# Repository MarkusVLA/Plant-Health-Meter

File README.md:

## Plant-health-meter
This repository contains Aalto AAN-C2009 project device hardware configuration and embedded software for a plant health monitoring system based on the ESP32c3 SoC.

## Features
- Soil moisture sensing
- Ambient light monitoring
- Temperature and humidity measurement
- Battery-powered operation with charging circuit
- Web interface for monitoring plant health 

## PCB
PCB design done in KiCad.

Schematic: [PDF](PCB/img/schematic.pdf)

## Key Components
- ESP32-C3 microcontroller
- BME280 temperature/humidity sensor
- Custom capacitive soil moisture sensor
- Photodiode and OPA340 based transimpedance amplifier
- ADS1115 16-bit ADC for accurate measurements

## Embedded software
Embedded software is written in C using the ESP-IDF (Espressif IoT Development Framework)
[ESP programming guide](https://docs.espressif.com/projects/esp-idf/en/v5.2.5/esp32c3/get-started/index.html)

## Pin Assignments
See the schematic for detailed I/O connections and sensor bus configuration.

## Setup Instructions
1. Follow the ESP-IDF installation guide
2. Clone this repository
3. In the `main/` folder create `private_config.h` file, with following definitions:
    1. `#define FIREBASE_HOST "xxx.firebasedatabase.app"` - url of the firebase realtime database
    2. `#define FIREBASE_AUTH ""` - authentication token for the firebase - (TODO: not tested yet with protected database)
4. Set ESP32-C3 target in the idf `idf.py set-target esp32c3`
5. Configure the partitions and BLE version `idf.py menuconfig`:
    1. Go to Partition Table → Partition Table and select Custom partition table CSV. Then set the path to `partitions.csv`.
    2. Go to Component Config → Bluetooth → Bluedroid BLE version and choose v4.0.
    3. Save and exit the configuration menu.
6. Build and flash using `idf.py build flash monitor`

## Connection Instructions

1. By default, there are no Wi-Fi credentials set. The device will immediately enter Bluetooth setup mode on boot.

2. For setup, you’ll need a mobile app capable of sending data over BLE, such as **nRF Connect**.

3. When the device is in Bluetooth setup mode, one of its LEDs will begin blinking. You can then find the device in the app under the name:  
   **`PLANT_SENSOR_01`**

4. Press **Connect** to establish a Bluetooth connection.

5. Once connected, look for **Advertised Services** in the device details. Find the characteristic that supports both **Read** and **Write**, and tap the **up arrow (⬆️)** to write data.

6. Select **UTF-8** as the encoding format and send a message with the following structure:  
   ```
   device_id:wifi_ssid:wifi_password
   ```

   For example:  
   ```
   sensor1:mywifi:secret_password
   ```

7. After sending the credentials, the device will restart and attempt to connect to the specified Wi-Fi network.

8. Once connected, sensor data will be sent to Firebase under the provided `device_id`.

---

**Important Notes:**
- `device_id` can contain only **letters, digits, and underscores** (e.g., `plant_sensor_1`).
- If the device fails to connect to Wi-Fi, it will re-enter Bluetooth setup mode on reboot.

## Power Requirements
3.7V Li-ion battery or USB power

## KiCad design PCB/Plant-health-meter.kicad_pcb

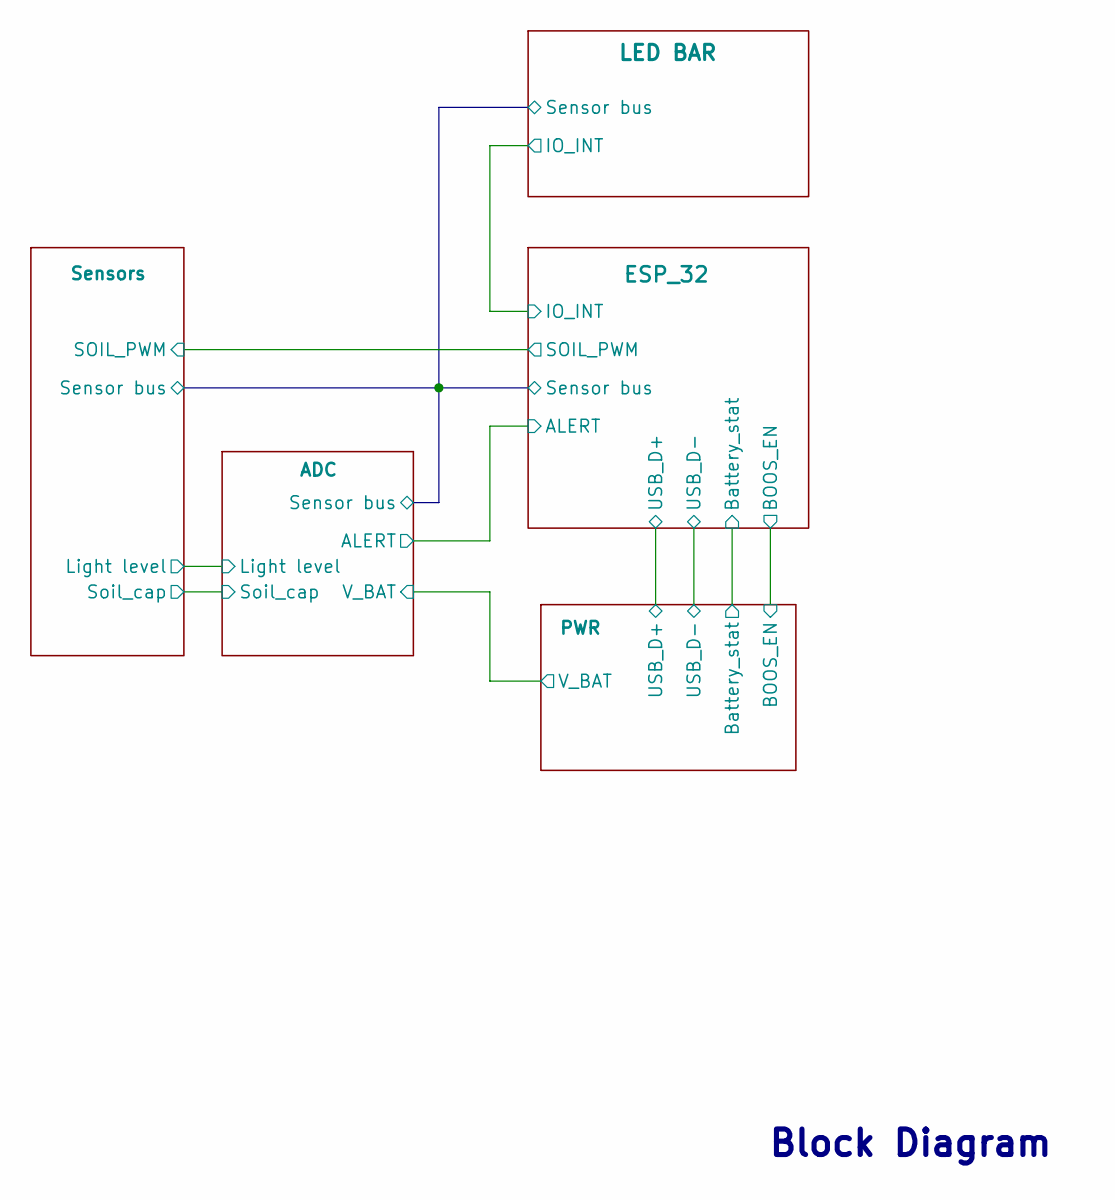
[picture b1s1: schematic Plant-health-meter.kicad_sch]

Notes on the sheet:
Block Diagram

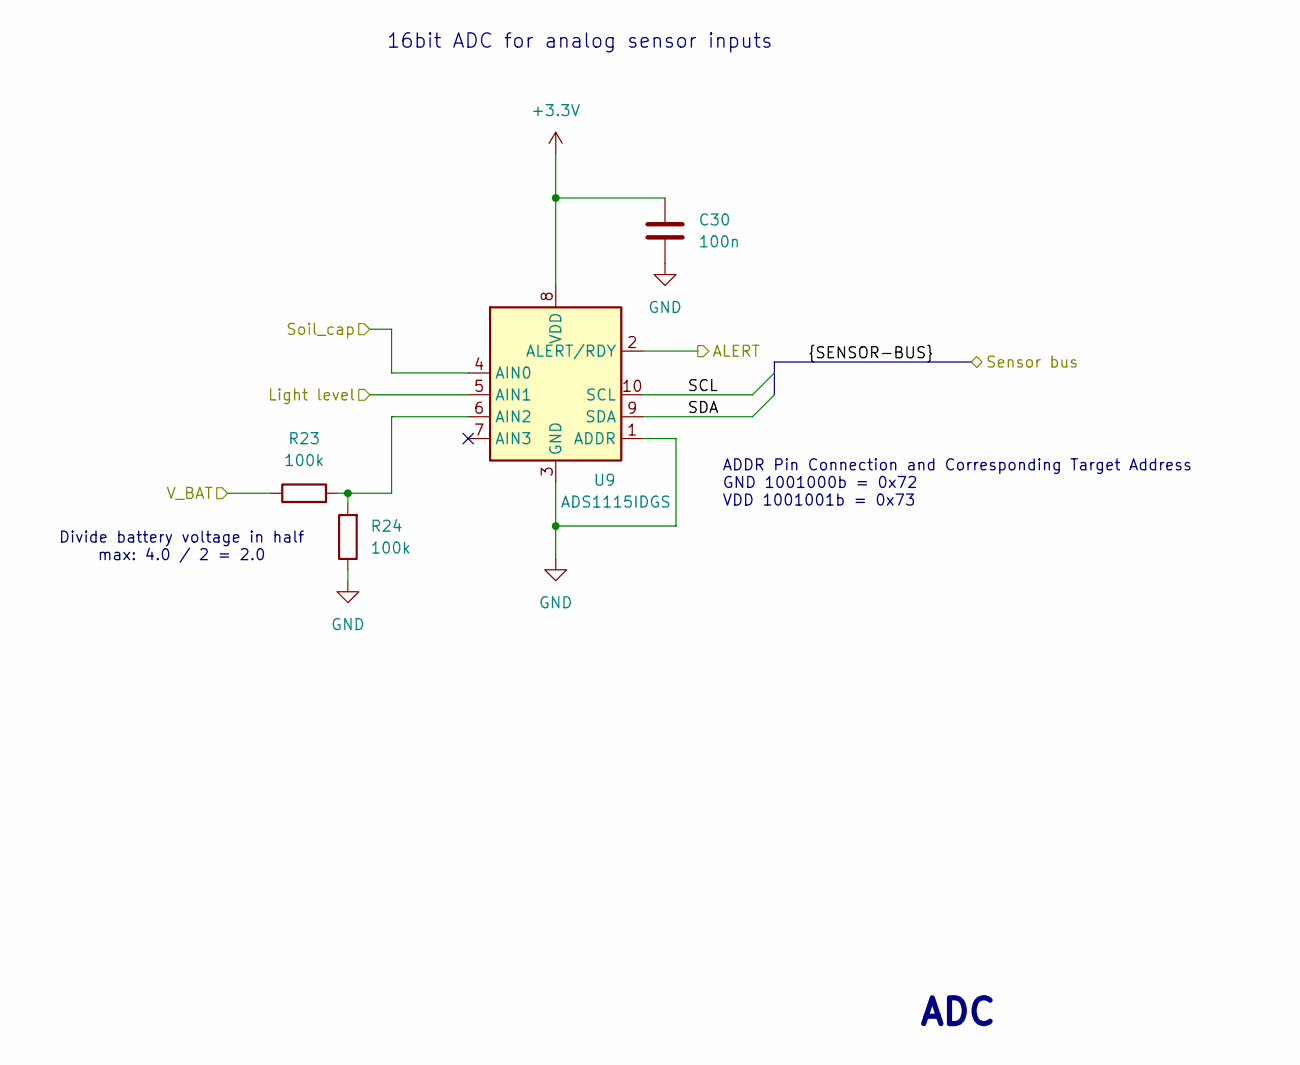
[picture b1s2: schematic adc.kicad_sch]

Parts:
C30: 100n; C_0402_1005Metric
R23, R24: 100k; R_0402_1005Metric
U9: ADS1115IDGS; TSSOP-10_3x3mm_P0.5mm

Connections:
+3.3V: C30.1, U9.8 (VDD); also elsewhere on the board
+BATT: R23.1; also elsewhere on the board
/ADC/ALERT: U9.2 (ALERT/RDY); also elsewhere on the board
/ADC/Light level: U9.5 (AIN1); also elsewhere on the board
/ADC/SCL: U9.10 (SCL); also elsewhere on the board
/ADC/SDA: U9.9 (SDA); also elsewhere on the board
/ADC/Soil_cap: U9.4 (AIN0); also elsewhere on the board
GND: C30.2, R24.1, U9.1 (ADDR), U9.3 (GND); also elsewhere on the board
unnamed: R23.2, R24.2, U9.6 (AIN2)

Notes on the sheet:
ADDR Pin Connection and Corresponding Target Address GND 1001000b = 0x72 VDD 1001001b = 0x73
Divide battery voltage in half max: 4.0 / 2 = 2.0
16bit ADC for analog sensor inputs
ADC

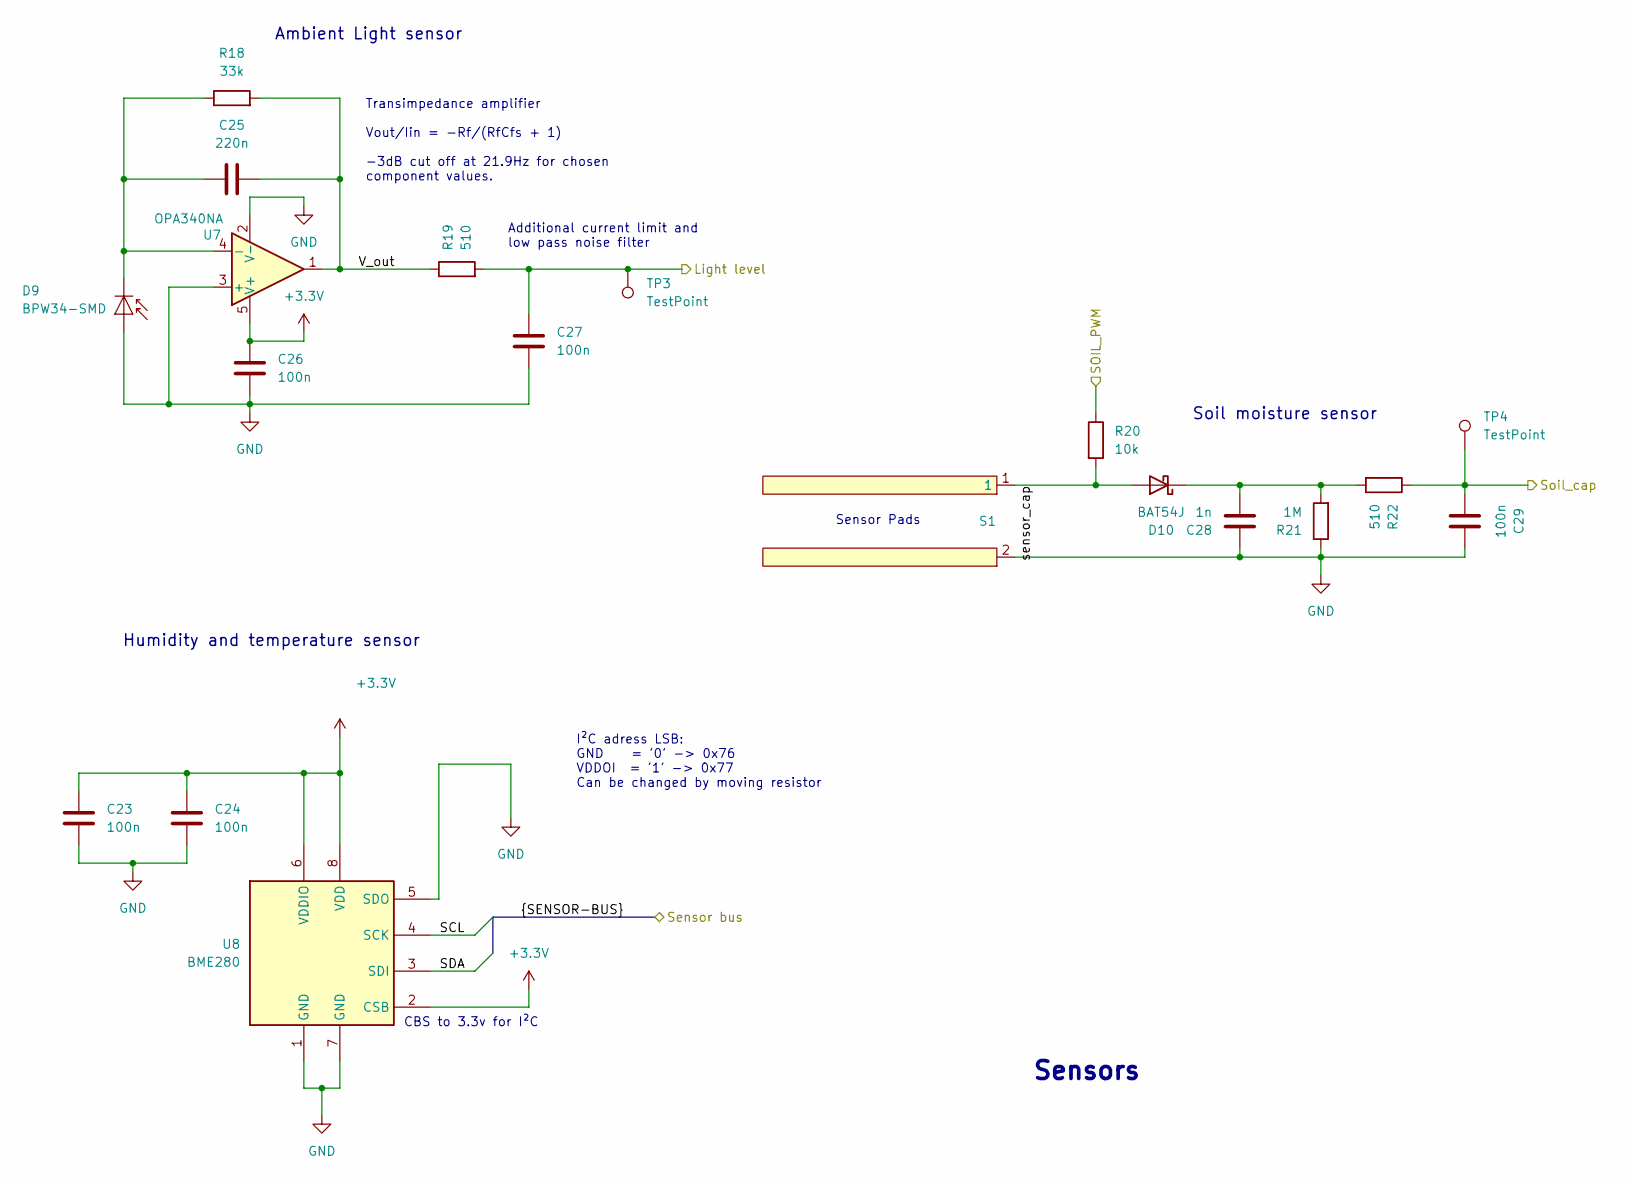
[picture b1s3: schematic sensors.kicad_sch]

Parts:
C23, C24, C26, C27, C29: 100n; C_0402_1005Metric
C25: 220n; C_0402_1005Metric
C28: 1n; C_0402_1005Metric
D9: BPW34-SMD; Osram_BPW34S-SMD
D10: BAT54J; D_SOD-323F
R18: 33k; R_0402_1005Metric
R19, R22: 510; R_0402_1005Metric
R20: 10k; R_0402_1005Metric
R21: 1M; R_0402_1005Metric
S1: Moisture_sensor_pads
TP3, TP4: TestPoint; TestPoint_Pad_D1.0mm
U7: OPA340NA; SOT-23-5
U8: BME280; Bosch_LGA-8_2.5x2.5mm_P0.65mm_ClockwisePinNumbering

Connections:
+3.3V: C23.1, C24.1, C26.1, U7.5 (V+), U8.2 (CSB), U8.6 (VDDIO), U8.8 (VDD); also elsewhere on the board
/ADC/Light level: C27.1, R19.2, TP3.1; also elsewhere on the board
/ADC/SCL: U8.4 (SCK); also elsewhere on the board
/ADC/SDA: U8.3 (SDI); also elsewhere on the board
/ADC/Soil_cap: C29.1, R22.1, TP4.1; also elsewhere on the board
/ESP_32/SOIL_PWM: R20.1; also elsewhere on the board
/Sensors/V_out: C25.2, R18.2, R19.1, U7.1
/Sensors/sensor_cap: D10.2 (A), R20.2, S1.1
GND: C23.2, C24.2, C26.2, C27.2, C28.1, C29.2, D9.2 (A), R21.1, S1.2, U7.2 (V-), U7.3 (+), U8.1 (GND), U8.5 (SDO), U8.7 (GND); also elsewhere on the board
unnamed: C25.1, D9.1 (K), R18.1, U7.4 (-)
unnamed: C28.2, D10.1 (K), R21.2, R22.2

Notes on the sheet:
CBS to 3.3v for I²C
Sensor Pads
I²C adress LSB: GND = '0' -> 0x76 VDDOI = '1' -> 0x77 Can be changed by moving resistor
Soil moisture sensor
Additional current limit and low pass noise filter
Transimpedance amplifier Vout/Iin = -Rf/(RfCfs + 1) -3dB cut off at 21.9Hz for chosen component values.
Humidity and temperature sensor
Sensors
Ambient Light sensor

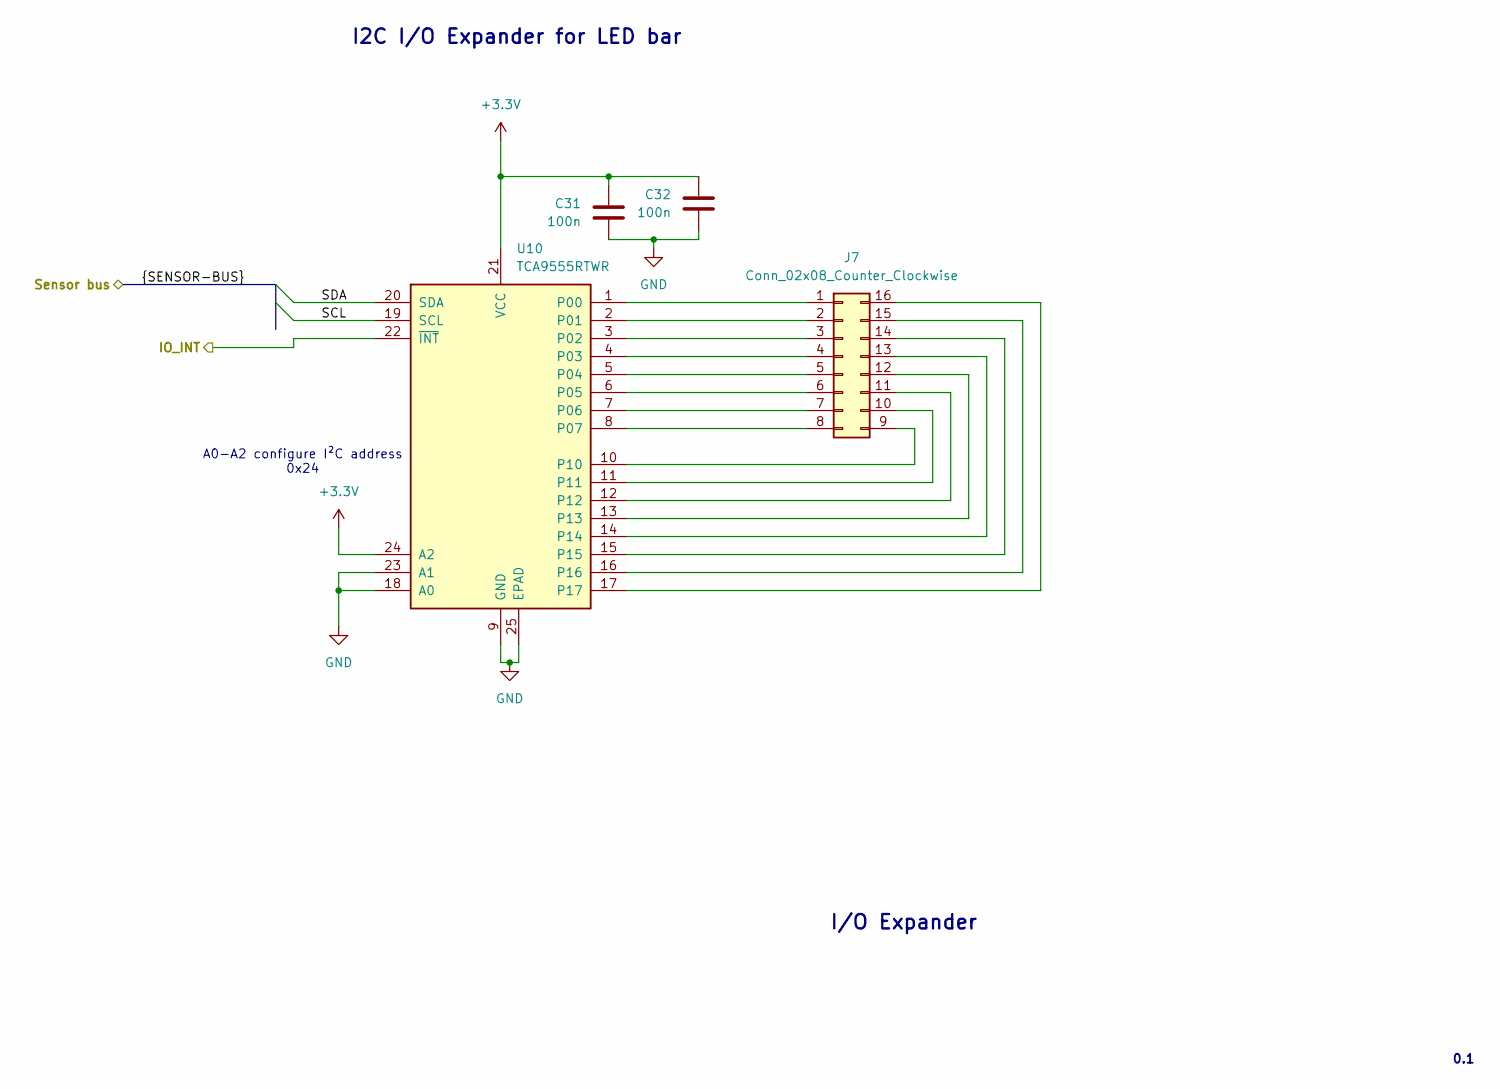
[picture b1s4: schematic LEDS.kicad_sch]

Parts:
C31, C32: 100n; C_0402_1005Metric
J7: Conn_02x08_Counter_Clockwise; PinHeader_2x08_P1.27mm_Vertical_SMD
U10: TCA9555RTWR; WQFN-24-1EP_4x4mm_P0.5mm_EP2.45x2.45mm

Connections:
+3.3V: C31.1, C32.1, U10.21 (VCC), U10.24 (A2); also elsewhere on the board
/ADC/SCL: U10.19 (SCL); also elsewhere on the board
/ADC/SDA: U10.20 (SDA); also elsewhere on the board
/ESP_32/IO_INT: U10.22 (~INT); also elsewhere on the board
GND: C31.2, C32.2, U10.9 (GND), U10.18 (A0), U10.23 (A1), U10.25 (EPAD); also elsewhere on the board
unnamed: J7.1, U10.1 (P00)
unnamed: J7.2, U10.2 (P01)
unnamed: J7.3, U10.3 (P02)
unnamed: J7.4, U10.4 (P03)
unnamed: J7.5, U10.5 (P04)
unnamed: J7.6, U10.6 (P05)
unnamed: J7.7, U10.7 (P06)
unnamed: J7.8, U10.8 (P07)
unnamed: J7.9, U10.10
unnamed: J7.10, U10.11
unnamed: J7.11, U10.12
unnamed: J7.12, U10.13
unnamed: J7.13, U10.14
unnamed: J7.14, U10.15
unnamed: J7.15, U10.16
unnamed: J7.16, U10.17

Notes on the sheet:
0.1
I2C I/O Expander for LED bar
A0-A2 configure I²C address 0x24
I/O Expander

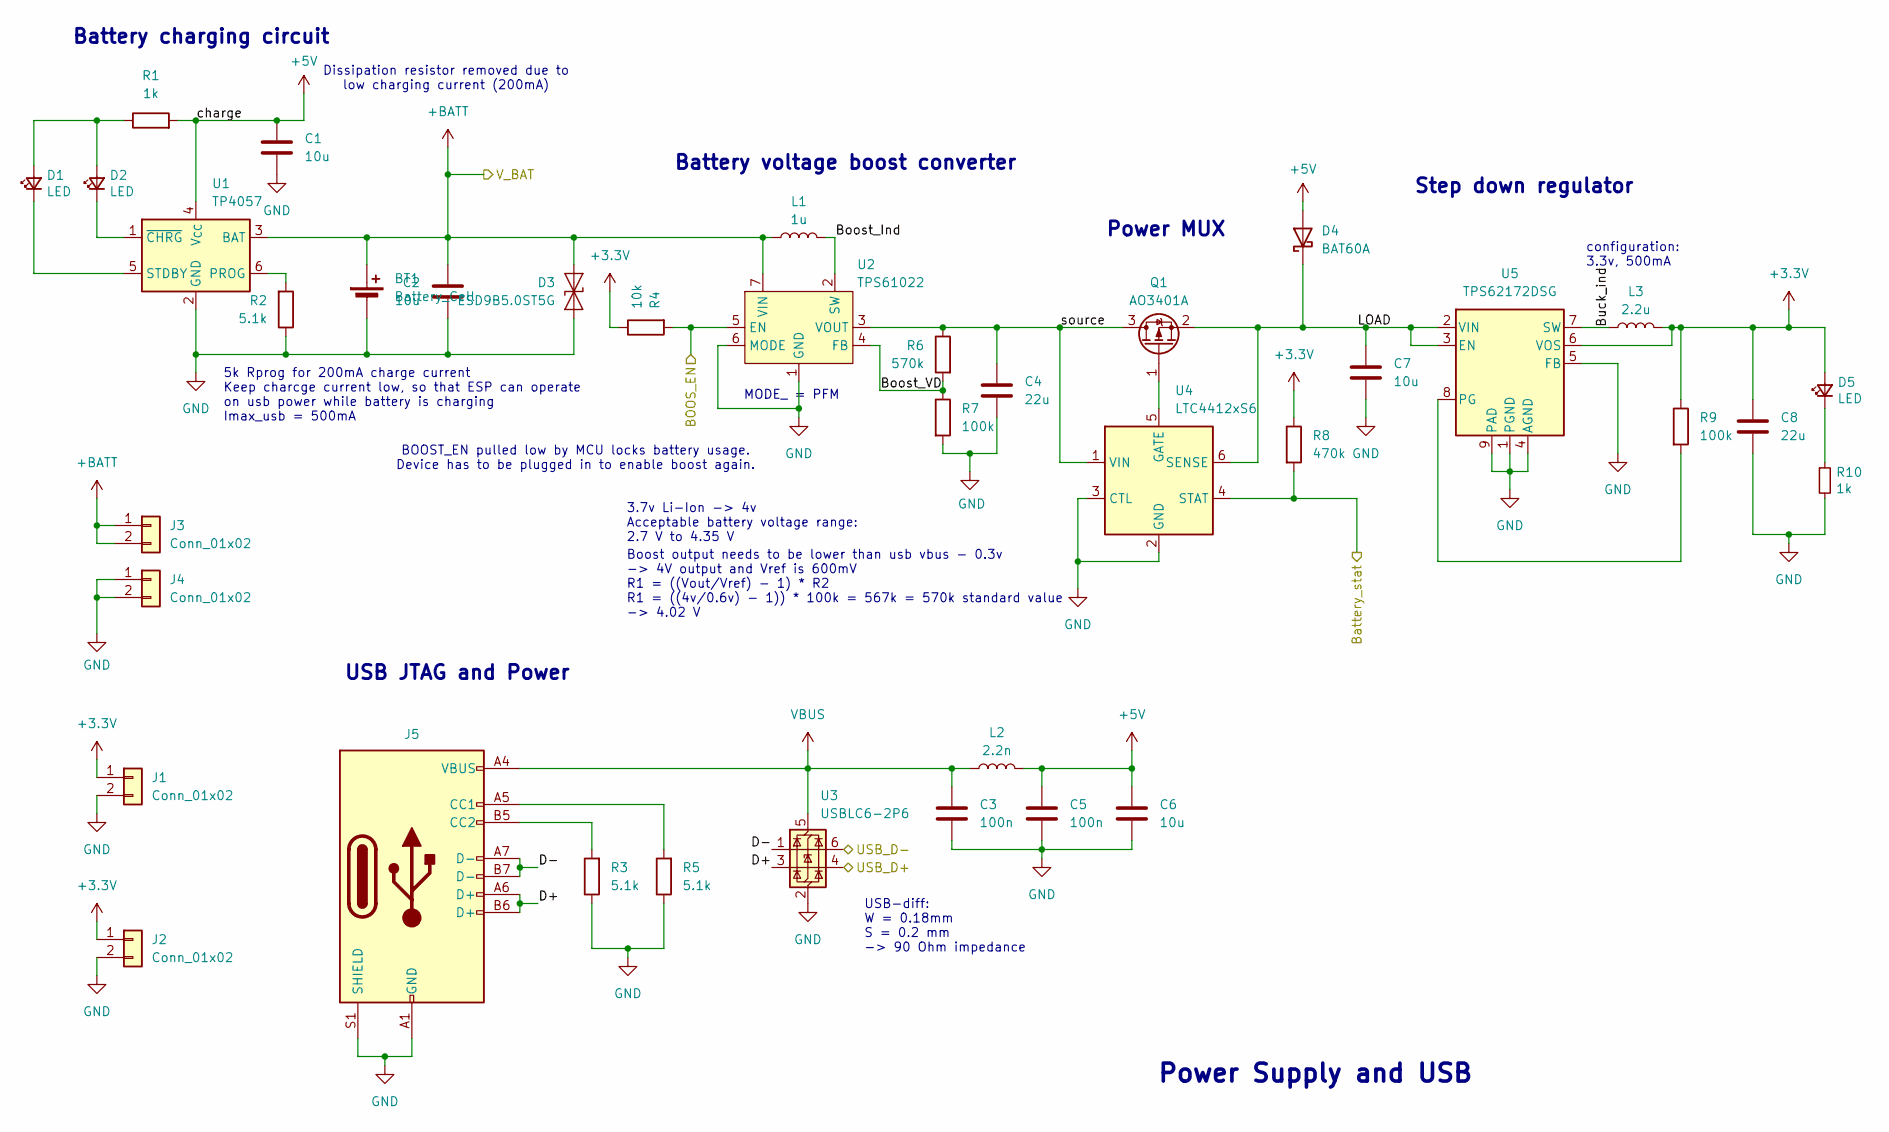
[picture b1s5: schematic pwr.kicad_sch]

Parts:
BT1: Battery_Cell
C1, C2, C6, C7: 10u; C_0603_1608Metric
C3, C5: 100n; C_0402_1005Metric
C4, C8: 22u; C_0805_2012Metric
D1, D2, D5: LED; LED_0805_2012Metric_Pad1.15x1.40mm_HandSolder; LCSC C205445
D3: ESD9B5.0ST5G; D_SOD-923
D4: BAT60A; D_SOD-323
J1, J2, J3, J4: Conn_01x02; PinHeader_1x02_P2.54mm_Vertical
J5: USB_C_Receptacle_USB2.0_14P; USB_C_Receptacle_HRO_TYPE-C-31-M-12
L1: 1u; L_0805_2012Metric
L2: 2.2n; L_0603_1608Metric
L3: 2.2u; L_1008_2520Metric
Q1: AO3401A; SOT-23
R1, R10: 1k; R_0402_1005Metric
R2, R3, R5: 5.1k; R_0402_1005Metric
R4: 10k; R_0402_1005Metric
R6: 570k; R_0402_1005Metric
R7, R9: 100k; R_0402_1005Metric
R8: 470k; R_0402_1005Metric
U1: TP4057; TSOT-23-6
U2: TPS61022; Texas_RWU0007A_VQFN-7_2x2mm_P0.5mm
U3: USBLC6-2P6; SOT-666
U4: LTC4412xS6; TSOT-23-6
U5: TPS62172DSG; WSON-8-1EP_2x2mm_P0.5mm_EP0.9x1.6mm_ThermalVias

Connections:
+3.3V: C8.1, D5.2 (A), J1.1, J2.1, L3.2, R4.1, R8.1, R9.1, U5.6 (VOS); also elsewhere on the board
+5V: C1.1, C5.1, C6.1, D4.2 (A), L2.2, R1.2, U1.4 (V_{CC})
+BATT: BT1.1 (+), C2.1, D3.2 (A2), J3.1, J3.2, L1.1, U1.3 (BAT), U2.7 (VIN); also elsewhere on the board
/ESP_32/BOOS_EN: R4.2, U2.5 (EN); also elsewhere on the board
/ESP_32/Battery_stat: R8.2, U4.4 (STAT); also elsewhere on the board
/ESP_32/USB_D+: U3.4 (I/O2); also elsewhere on the board
/ESP_32/USB_D-: U3.6 (I/O1); also elsewhere on the board
/PWR/Boost_Ind: L1.2, U2.2 (SW)
/PWR/Boost_VD: R6.2, R7.1, U2.4 (FB)
/PWR/Buck_ind: L3.1, U5.7 (SW)
/PWR/D+: J5.A6 (D+), J5.B6 (D+), U3.3 (I/O2)
/PWR/D-: J5.A7 (D-), J5.B7 (D-), U3.1 (I/O1)
/PWR/LOAD: C7.1, D4.1 (K), Q1.2 (S), U4.6 (SENSE), U5.2 (VIN), U5.3 (EN)
/PWR/source: C4.1, Q1.3 (D), R6.1, U2.3 (VOUT), U4.1 (VIN)
GND: BT1.2 (-), C1.2, C2.2, C3.2, C4.2, C5.2, C6.2, C7.2, C8.2, D3.1 (A1), J1.2, J2.2, J4.1, J4.2, J5.A1 (GND), J5.A12 (GND), J5.B1 (GND), J5.B12 (GND), J5.S1 (SHIELD), R2.1, R3.1, R5.1, R7.2, R10.2, U1.2 (GND), U2.1 (GND), U2.6 (MODE), U3.2 (GND), U4.2 (GND), U4.3 (CTL), U5.1 (PGND), U5.4 (AGND), U5.5 (FB), U5.9 (PAD); also elsewhere on the board
unnamed: D1.2 (A), D2.2 (A), R1.1
unnamed: D1.1 (K), U1.5 (STDBY)
unnamed: D2.1 (K), U1.1 (~CHRG)
unnamed: D5.1 (K), R10.1
unnamed: J5.A5 (CC1), R5.2
unnamed: J5.B5 (CC2), R3.2
unnamed: Q1.1 (G), U4.5 (GATE)
unnamed: R2.2, U1.6 (PROG)
unnamed: R9.2, U5.8 (PG)
VBUS: C3.1, J5.A4 (VBUS), J5.A9 (VBUS), J5.B4 (VBUS), J5.B9 (VBUS), L2.1, U3.5 (VBUS)

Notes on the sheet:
configuration: 3.3v, 500mA
MODE_ = PFM
Power MUX
Dissipation resistor removed due to low charging current (200mA)
BOOST_EN pulled low by MCU locks battery usage. Device has to be plugged in to enable boost again.
5k Rprog for 200mA charge current Keep charcge current low, so that ESP can operate on usb power while battery is charging Imax_usb = 500mA
Battery charging circuit
USB JTAG and Power
USB-diff: W = 0.18mm S = 0.2 mm -> 90 Ohm impedance
Boost output needs to be lower than usb vbus - 0.3v -> 4V output and Vref is 600mV R1 = ((Vout/Vref) - 1) * R2 R1 = ((4v/0.6v) - 1)) * 100k = 567k = 570k standard value -> 4.02 V
Battery voltage boost converter
3.7v Li-Ion -> 4v Acceptable battery voltage range: 2.7 V to 4.35 V
Step down regulator
Power Supply and USB

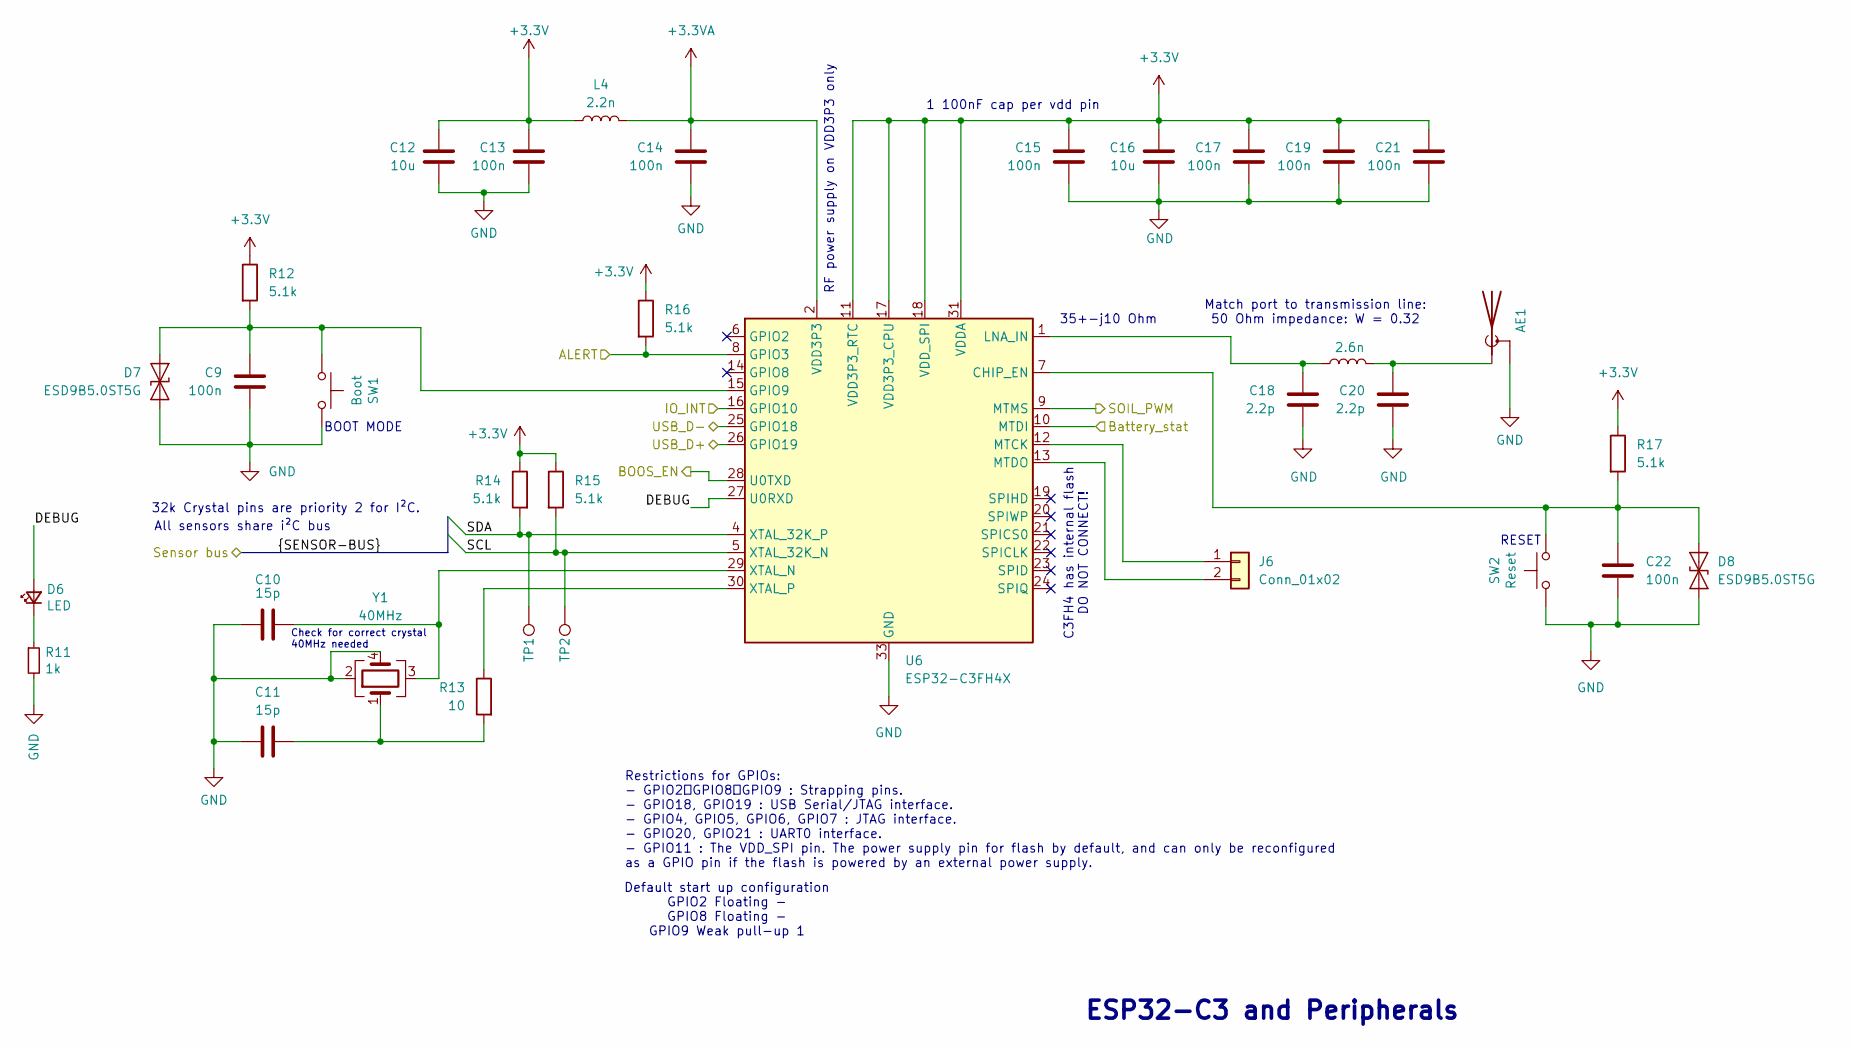
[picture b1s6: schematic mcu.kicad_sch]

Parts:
AE1: Antenna_Shield; Texas_SWRA117D_2.4GHz_Left
C9, C13, C14, C15, C17, C19, C21, C22: 100n; C_0402_1005Metric
C10, C11: 15p; C_0402_1005Metric
C12, C16: 10u; C_0603_1608Metric
C18, C20: 2.2p; C_0402_1005Metric
D6: LED; LED_0805_2012Metric_Pad1.15x1.40mm_HandSolder; LCSC C205445
D7, D8: ESD9B5.0ST5G; D_SOD-923
J6: Conn_01x02; PinHeader_1x02_P2.54mm_Vertical
L4: 2.2n; L_0402_1005Metric
L5: 2.6n; L_0402_1005Metric
R11: 1k; R_0402_1005Metric
R12, R14, R15, R16, R17: 5.1k; R_0402_1005Metric
R13: 10; R_0402_1005Metric
SW1: Boot; SW_Push_SPST_NO_Alps_SKRK; LCSC C115357
SW2: Reset; SW_Push_SPST_NO_Alps_SKRK; LCSC C115357
TP1, TP2: TestPoint; TestPoint_Pad_D1.0mm
U6: ESP32-C3FH4X; QFN-32-1EP_5x5mm_P0.5mm_EP3.7x3.7mm
Y1: 40MHz; Crystal_SMD_3225-4Pin_3.2x2.5mm

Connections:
+3.3V: C12.1, C13.1, C15.1, C16.1, C17.1, C19.1, C21.1, L4.2, R12.1, R14.1, R15.1, R16.1, R17.1, U6.11 (VDD3P3_RTC), U6.17 (VDD3P3_CPU), U6.18 (VDD_SPI), U6.31 (VDDA), U6.32 (VDDA); also elsewhere on the board
+3.3VA: C14.1, L4.1, U6.2 (VDD3P3), U6.3 (VDD3P3)
/ADC/ALERT: R16.2, U6.8 (GPIO3); also elsewhere on the board
/ADC/SCL: R15.2, TP2.1, U6.5 (XTAL_32K_N); also elsewhere on the board
/ADC/SDA: R14.2, TP1.1, U6.4 (XTAL_32K_P); also elsewhere on the board
/ESP_32/BOOS_EN: U6.28 (U0TXD); also elsewhere on the board
/ESP_32/Battery_stat: U6.10 (MTDI); also elsewhere on the board
/ESP_32/DEBUG: D6.2 (A), U6.27 (U0RXD)
/ESP_32/IO_INT: U6.16 (GPIO10); also elsewhere on the board
/ESP_32/SOIL_PWM: U6.9 (MTMS); also elsewhere on the board
/ESP_32/USB_D+: U6.26 (GPIO19); also elsewhere on the board
/ESP_32/USB_D-: U6.25 (GPIO18); also elsewhere on the board
GND: AE1.2 (Shield), C9.1, C10.1, C11.1, C12.2, C13.2, C14.2, C15.2, C16.2, C17.2, C18.2, C19.2, C20.2, C21.2, C22.2, D7.1 (A1), D8.1 (A1), R11.2, SW1.2, SW2.2, U6.33 (GND), Y1.2, Y1.4; also elsewhere on the board
unnamed: AE1.1 (A), C20.1, L5.1
unnamed: C11.2, R13.2, Y1.1
unnamed: D6.1 (K), R11.1
unnamed: C9.2, D7.2 (A2), R12.2, SW1.1, U6.15 (GPIO9)
unnamed: C22.1, D8.2 (A2), R17.2, SW2.1, U6.7 (CHIP_EN)
unnamed: J6.1, U6.12 (MTCK)
unnamed: J6.2, U6.13 (MTDO)
unnamed: C18.1, L5.2, U6.1 (LNA_IN)
unnamed: C10.2, U6.29 (XTAL_N), Y1.3
unnamed: R13.1, U6.30 (XTAL_P)

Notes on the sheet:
Match port to transmission line: 50 Ohm impedance: W = 0.32
32k Crystal pins are priority 2 for I²C.
RESET
ESP32-C3 and Peripherals
BOOT MODE
RF power supply on VDD3P3 only
C3FH4 has internal flash DO NOT CONNECT!
35+-j10 Ohm
Default start up configuration GPIO2 Floating - GPIO8 Floating - GPIO9 Weak pull-up 1
All sensors share i²C bus
Check for correct crystal 40MHz needed
1 100nF cap per vdd pin
Restrictions for GPIOs: - GPIO2、GPIO8、GPIO9 : Strapping pins. - GPIO18, GPIO19 : USB Serial/JTAG interface. - GPIO4, GPIO5, GPIO6, GPIO7 : JTAG interface. - GPIO20, GPIO21 : UART0 interface. - GPIO11 : The VDD_SPI pin. The power supply pin for flash by default, and can only be reconfigured as a GPI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

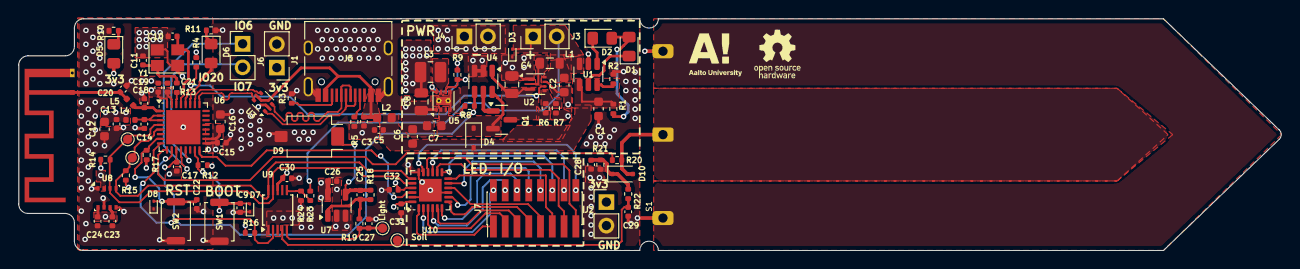
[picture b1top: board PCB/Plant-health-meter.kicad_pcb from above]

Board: 4 copper layers, 136.2 x 25.0 mm, 98 parts (0 on the bottom side), 65 nets.

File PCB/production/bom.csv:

Designator,Footprint,Quantity,Value,LCSC Part #
AE1,Texas_SWRA117D_2.4GHz_Left,1,Antenna_Shield,
"C1, C12, C16, C2, C6, C7",0603,6,10u,
"C10, C11",0402,2,15p,
"C13, C14, C15, C17, C19, C21, C22, C23, C24, C26, C27, C29, C3, C30, C31, C32, C5, C9",0402,18,100n,
"C18, C20",0402,2,2.2p,
C25,0402,1,220n,
C28,0402,1,1n,
"C4, C8",0805,2,22u,
"D1, D2, D5, D6",0805,4,LED,C205445
D10,D_SOD-323F,1,BAT54J,
"D3, D7, D8",D_SOD-923,3,ESD9B5.0ST5G,
D4,D_SOD-323,1,BAT60A,
D9,Osram_BPW34S-SMD,1,BPW34-SMD,
"J1, J2, J3, J4, J6",PinHeader_1x02_P2.54mm_Vertical,5,Conn_01x02,
J5,USB_C_Receptacle_HRO_TYPE-C-31-M-12,1,USB_C_Receptacle_USB2.0_14P,
J7,PinHeader_2x08_P1.27mm_Vertical_SMD,1,Conn_02x08_Counter_Clockwise,
L1,0805,1,1u,
L2,0603,1,2.2n,
L3,1008,1,2.2u,
L4,0402,1,2.2n,
L5,0402,1,2.6n,
Q1,SOT-23,1,AO3401A,
R1,0402,1,1k,
"R10, R11",0402,2,1k,
"R12, R14, R15, R16, R17, R2, R3, R5",0402,8,5.1k,
R13,0402,1,10,
R18,0402,1,33k,
"R19, R22",0402,2,510,
"R20, R4",0402,2,10k,
R21,0402,1,1M,
"R23, R24, R7, R9",0402,4,100k,
R6,0402,1,570k,
R8,0402,1,470k,
S1,Moisture_sensor_pads,1,~,
SW1,SW_Push_SPST_NO_Alps_SKRK,1,Boot,C115357
SW2,SW_Push_SPST_NO_Alps_SKRK,1,Reset,C115357
"TP1, TP2, TP3, TP4",TestPoint_Pad_D1.0mm,4,TestPoint,
U1,TSOT-23-6,1,TP4057,
U10,WQFN-24-1EP_4x4mm_P0.5mm_EP2.45x2.45mm,1,TCA9555RTWR,
U2,Texas_RWU0007A_VQFN-7_2x2mm_P0.5mm,1,TPS61022,
U3,SOT-666,1,USBLC6-2P6,
U4,TSOT-23-6,1,LTC4412xS6,
U5,WSON-8-1EP_2x2mm_P0.5mm_EP0.9x1.6mm_ThermalVias,1,TPS62172DSG,
U6,QFN-32-1EP_5x5mm_P0.5mm_EP3.7x3.7mm,1,ESP32-C3FH4X,
U7,SOT-23-5,1,OPA340NA,
U8,Bosch_LGA-8_2.5x2.5mm_P0.65mm_ClockwisePinNumbering,1,BME280,
U9,TSSOP-10_3x3mm_P0.5mm,1,ADS1115IDGS,
Y1,Crystal_SMD_3225-4Pin_3.2x2.5mm,1,40MHz,

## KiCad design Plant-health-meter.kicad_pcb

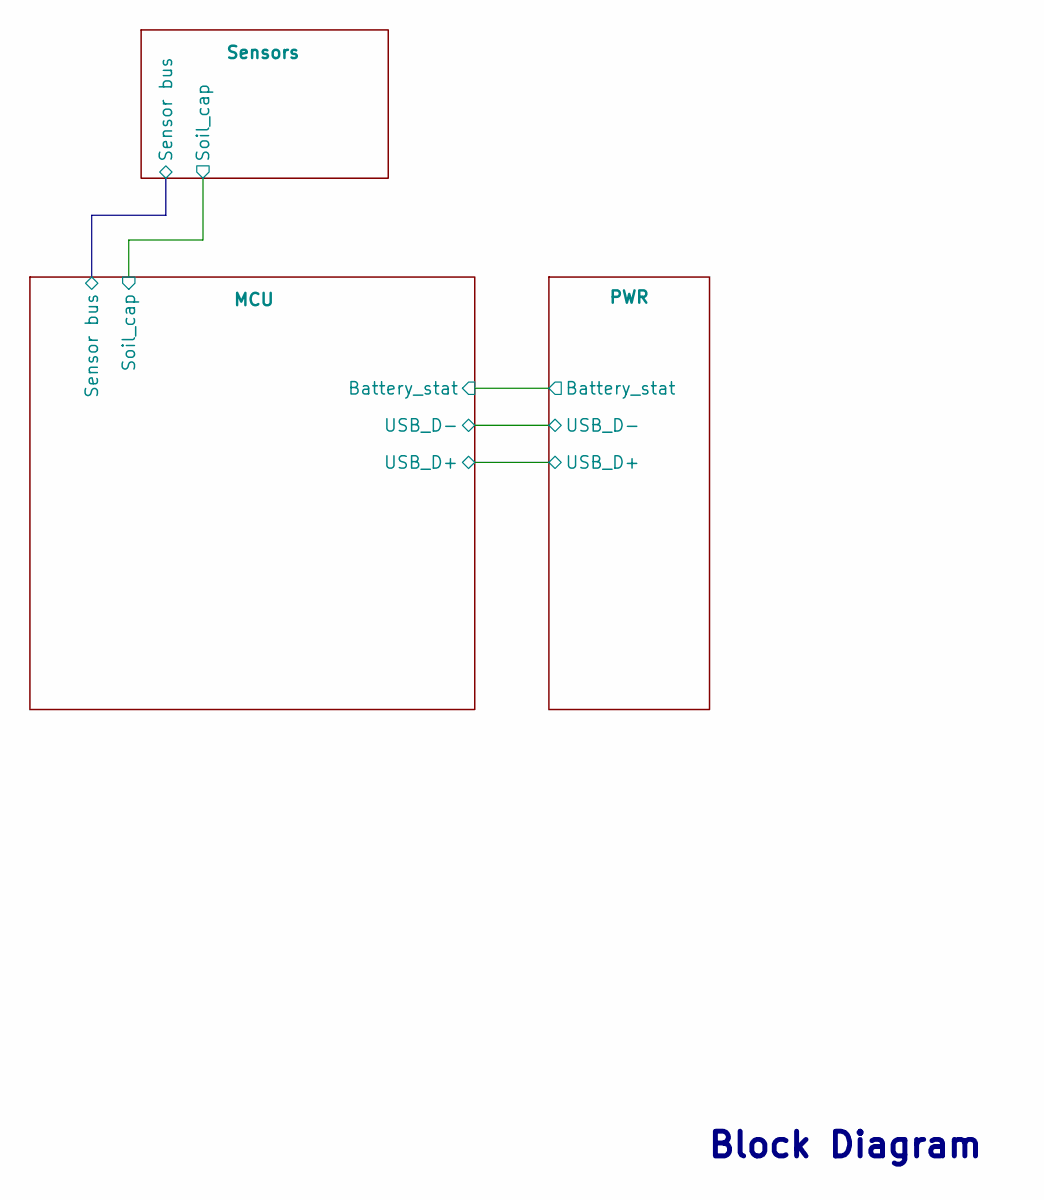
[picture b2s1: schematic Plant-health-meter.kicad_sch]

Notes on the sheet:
Block Diagram

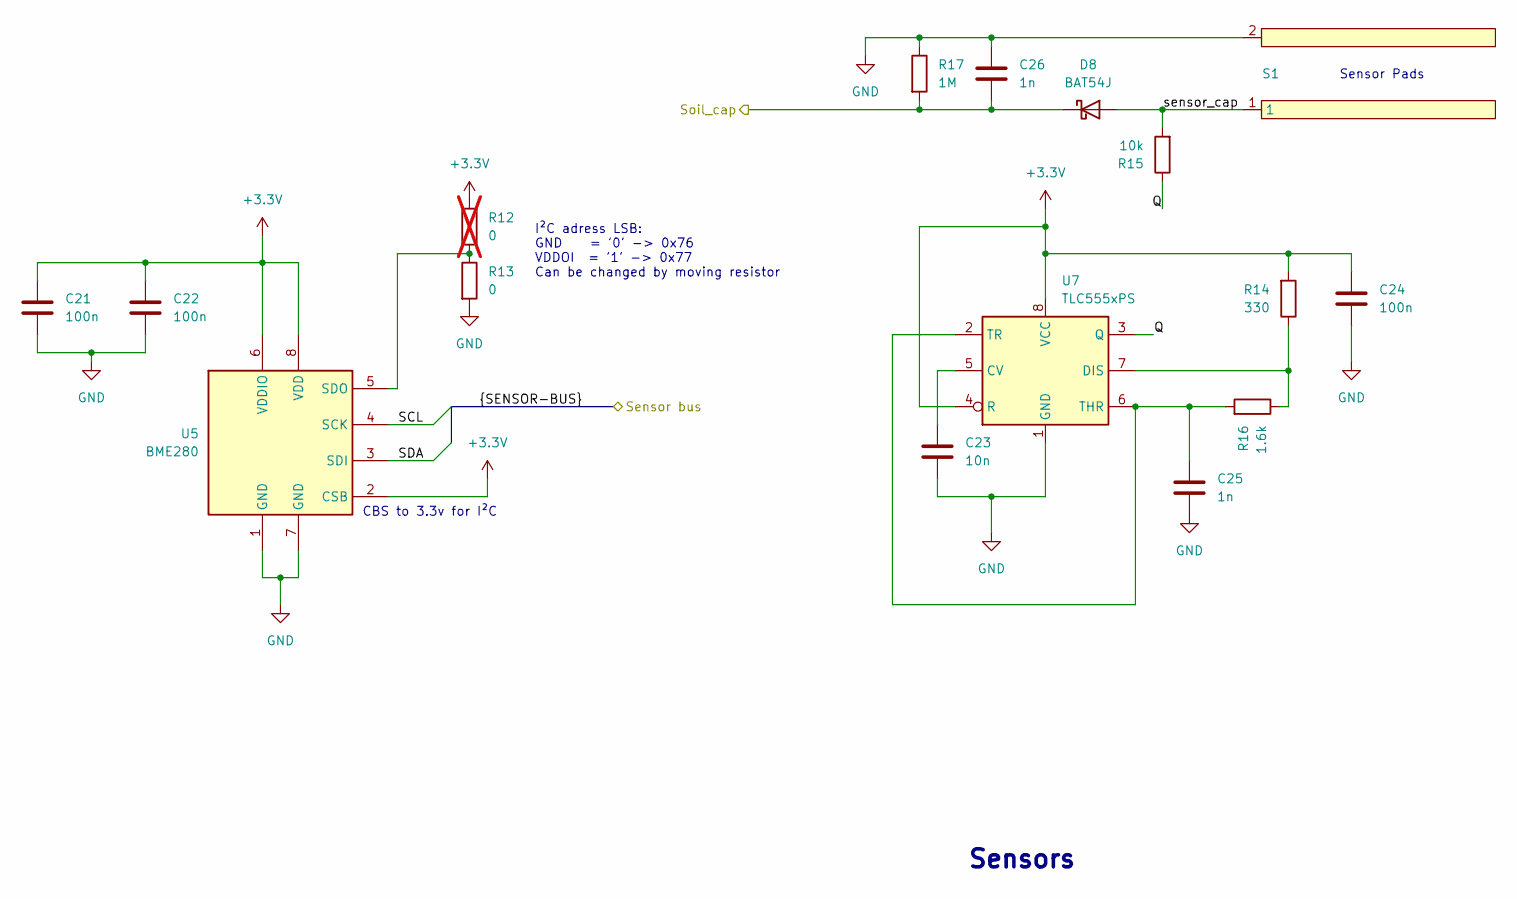
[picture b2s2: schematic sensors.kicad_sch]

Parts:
C21, C22, C24: 100n; C_0402_1005Metric
C23: 10n; C_0402_1005Metric
C25, C26: 1n; C_0402_1005Metric
D8: BAT54J; D_SOD-323F
R12: 0; R_0603_1608Metric; not fitted
R13: 0; R_0603_1608Metric
R14: 330; R_0603_1608Metric
R15: 10k; R_0402_1005Metric
R16: 1.6k; R_0603_1608Metric
R17: 1M; R_0402_1005Metric
S1: Moisture_sensor_pads
U5: BME280; Bosch_LGA-8_2.5x2.5mm_P0.65mm_ClockwisePinNumbering
U7: TLC555xPS; VSSOP-8_3x3mm_P0.65mm

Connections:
+3.3V: C21.1, C22.1, C24.1, R12.1, R14.2, U5.2 (CSB), U5.6 (VDDIO), U5.8 (VDD), U7.4 (R), U7.8 (VCC); also elsewhere on the board
/MCU/SCL: U5.4 (SCK); also elsewhere on the board
/MCU/SDA: U5.3 (SDI); also elsewhere on the board
/MCU/Soil_cap: C26.2, D8.1 (K), R17.2; also elsewhere on the board
/Sensors/Q: R15.1, U7.3 (Q)
/Sensors/sensor_cap: D8.2 (A), R15.2, S1.1
GND: C21.2, C22.2, C23.2, C24.2, C25.2, C26.1, R13.2, R17.1, S1.2, U5.1 (GND), U5.7 (GND), U7.1 (GND); also elsewhere on the board
unnamed: R12.2, R13.1, U5.5 (SDO)
unnamed: C23.1, U7.5 (CV)
unnamed: R14.1, R16.1, U7.7 (DIS)
unnamed: C25.1, R16.2, U7.2 (TR), U7.6 (THR)

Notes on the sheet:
CBS to 3.3v for I²C
Sensor Pads
I²C adress LSB: GND = '0' -> 0x76 VDDOI = '1' -> 0x77 Can be changed by moving resistor
Sensors
